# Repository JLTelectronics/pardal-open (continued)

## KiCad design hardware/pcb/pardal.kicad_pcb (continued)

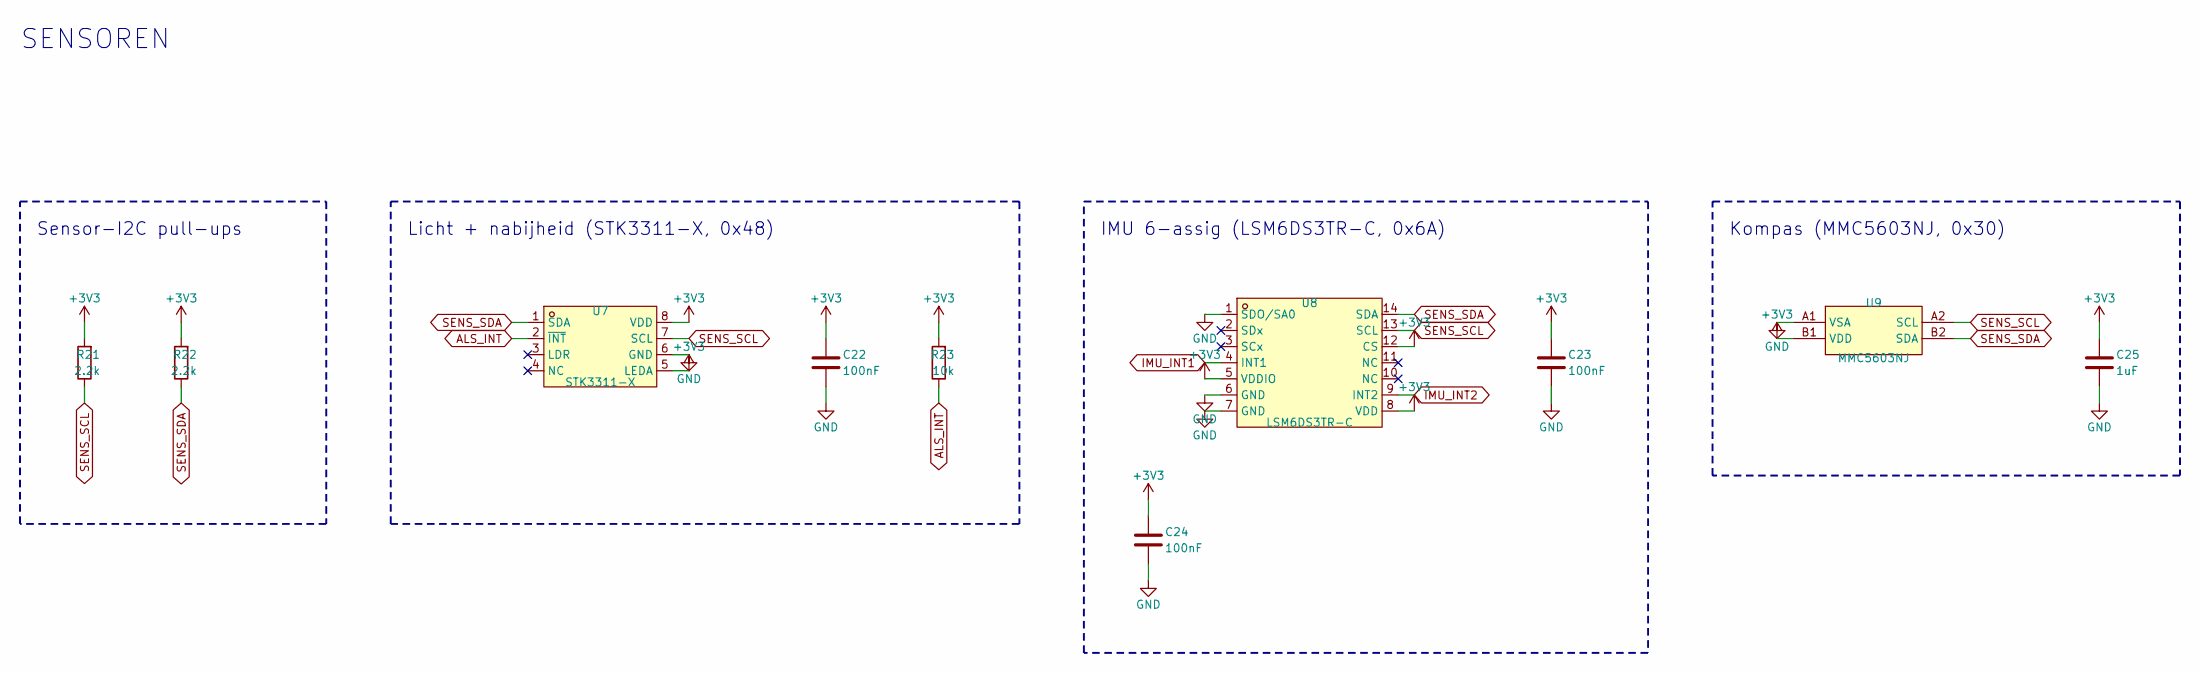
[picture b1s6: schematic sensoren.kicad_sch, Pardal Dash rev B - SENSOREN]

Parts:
C22, C23, C24: 100nF; C_0402_1005Metric; LCSC C1525
C25: 1uF; C_0402_1005Metric; LCSC C52923
R21, R22: 2.2k; R_0402_1005Metric; LCSC C25879
R23: 10k; R_0402_1005Metric; LCSC C25744
U7: STK3311-X; LGA-8_L4.0-W2.4-P0.97-BR; LCSC C966926
U8: LSM6DS3TR-C; LGA-14_L3.0-W2.5-P0.50-TL; LCSC C967633
U9: MMC5603NJ; FLIPCHIP-4_L0.8-W0.8-R2-C2-P0.40-TL; LCSC C404328

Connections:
+3V3: C22.1, C23.1, C24.1, C25.1, R21.2, R22.2, R23.2, U7.5 (LEDA), U7.8 (VDD), U8.5 (VDDIO), U8.8 (VDD), U8.12 (CS), U9.B1 (VDD); also elsewhere on the board
ALS_INT: R23.1, U7.2 (~INT); also elsewhere on the board
GND: C22.2, C23.2, C24.2, C25.2, U7.6 (GND), U8.1 (SDO/SA0), U8.6 (GND), U8.7 (GND), U9.A1 (VSA); also elsewhere on the board
IMU_INT1: U8.4 (INT1); also elsewhere on the board
IMU_INT2: U8.9 (INT2); also elsewhere on the board
SENS_SCL: R21.1, U7.7 (SCL), U8.13 (SCL), U9.A2 (SCL); also elsewhere on the board
SENS_SDA: R22.1, U7.1 (SDA), U8.14 (SDA), U9.B2 (SDA); also elsewhere on the board

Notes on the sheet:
SENSOREN
Sensor-I2C pull-ups
Licht + nabijheid (STK3311-X, 0x48)
IMU 6-assig (LSM6DS3TR-C, 0x6A)
Kompas (MMC5603NJ, 0x30)

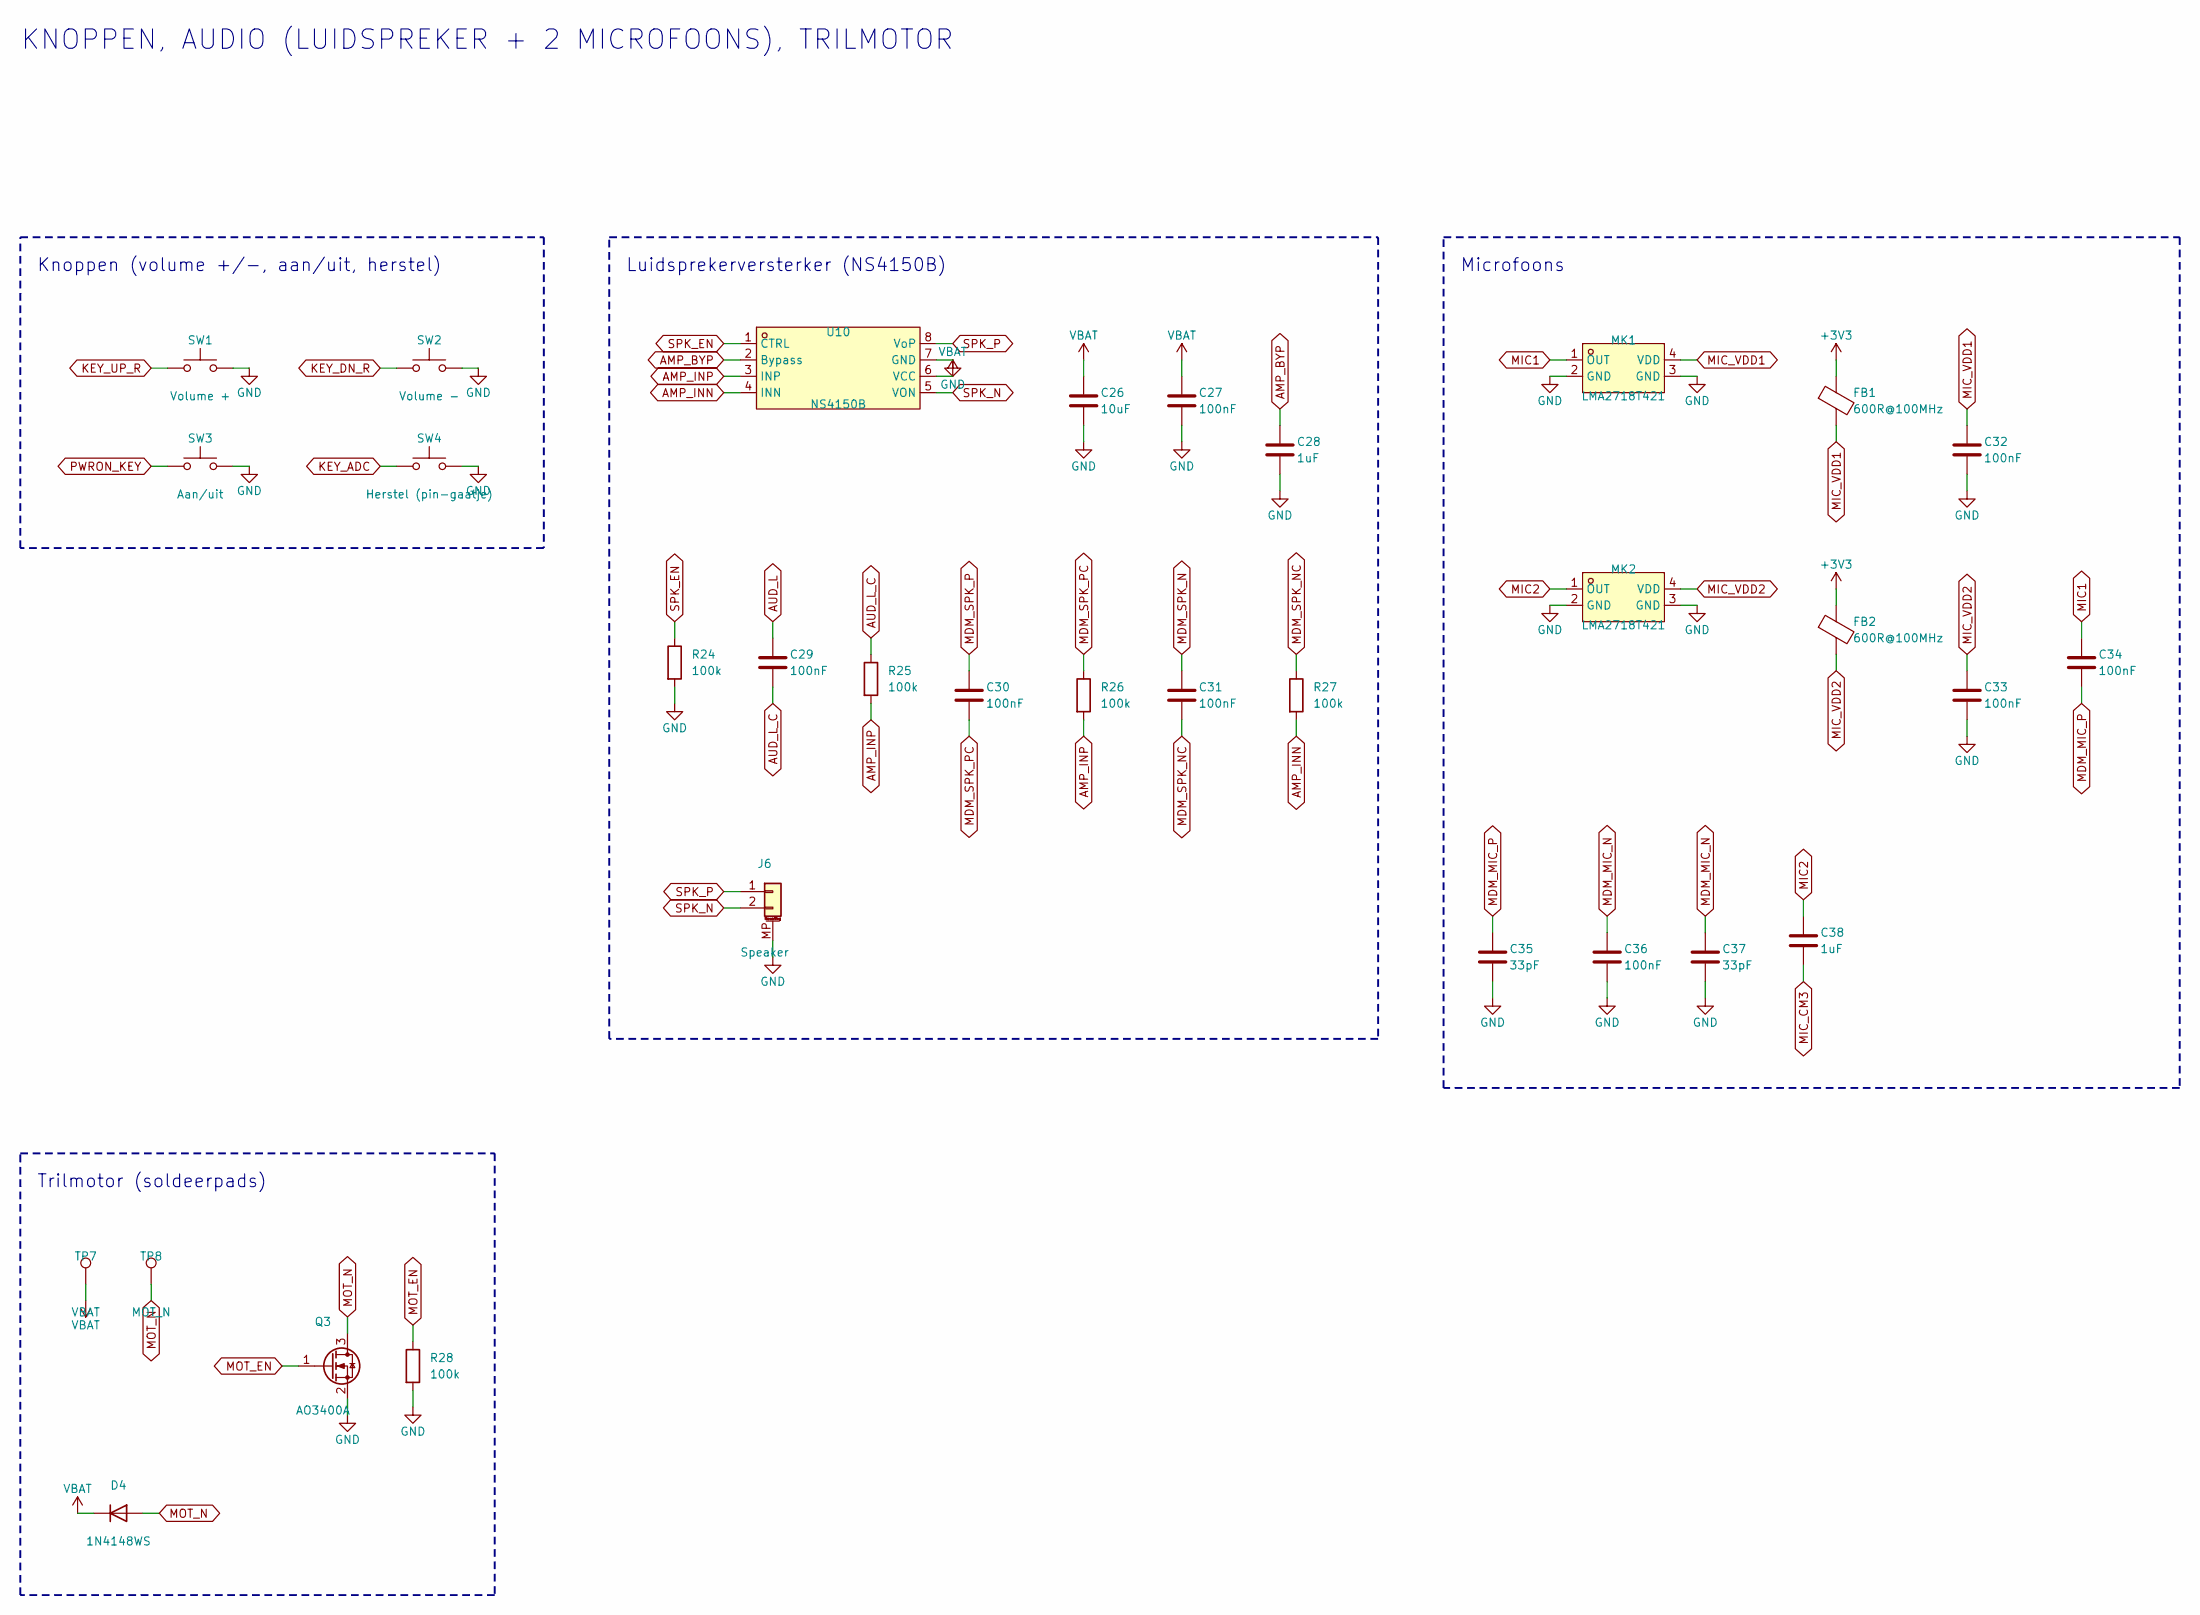
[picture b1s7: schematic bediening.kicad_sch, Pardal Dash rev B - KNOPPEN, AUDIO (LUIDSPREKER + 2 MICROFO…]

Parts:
C26: 10uF; C_0603_1608Metric; LCSC C19702
C27, C29, C30, C31, C32, C33, C34, C36: 100nF; C_0402_1005Metric; LCSC C1525
C28, C38: 1uF; C_0402_1005Metric; LCSC C52923
C35, C37: 33pF; C_0402_1005Metric; LCSC C1562
D4: 1N4148WS; D_SOD-323; LCSC C2128
FB1, FB2: 600R@100MHz; L_0402_1005Metric; LCSC C181004
J6: Speaker; JST_SH_SM02B-SRSS-TB_1x02-1MP_P1.00mm_Horizontal; LCSC C19271996
MK1, MK2: LMA2718T421; MIC-SMD_4P-L2.8-W1.9-P1.84-TL; LCSC C7587901
Q3: AO3400A; SOT-23; LCSC C20917
R24, R25, R26, R27, R28: 100k; R_0402_1005Metric; LCSC C25741
SW1: Volume +; SW_Push_1P1T-MP_NO_Horizontal_Alps_SKRTLAE010; LCSC C110293
SW2: Volume -; SW_Push_1P1T-MP_NO_Horizontal_Alps_SKRTLAE010; LCSC C110293
SW3: Aan/uit; SW_Push_1P1T_XKB_TS-1187A; LCSC C318884
SW4: Herstel (pin-gaatje); SW_SPST_TS-1088-xR020; LCSC C720477
TP7: VBAT; TestPoint_Pad_2.0x2.0mm
TP8: MOT_N; TestPoint_Pad_2.0x2.0mm
U10: NS4150B; MSOP-8_L3.0-W3.0-P0.65-LS5.0-BL; LCSC C189961

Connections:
+3V3: FB1.1, FB2.1; also elsewhere on the board
AMP_BYP: C28.1, U10.2 (Bypass)
AMP_INN: R27.2, U10.4 (INN)
AMP_INP: R25.2, R26.2, U10.3 (INP)
AUD_L: C29.1; also elsewhere on the board
AUD_L_C: C29.2, R25.1
GND: C26.2, C27.2, C28.2, C32.2, C33.2, C35.2, C36.2, C37.2, J6.MP (MountPin), MK1.2 (GND), MK1.3 (GND), MK2.2 (GND), MK2.3 (GND), Q3.2 (S), R24.2, R28.2, SW1.2, SW2.2, SW3.2, SW4.2, U10.7 (GND); also elsewhere on the board
KEY_ADC: SW4.1; also elsewhere on the board
KEY_DN_R: SW2.1; also elsewhere on the board
KEY_UP_R: SW1.1; also elsewhere on the board
MDM_MIC_N: C36.1, C37.1; also elsewhere on the board
MDM_MIC_P: C34.2, C35.1; also elsewhere on the board
MDM_SPK_N: C31.1; also elsewhere on the board
MDM_SPK_NC: C31.2, R27.1
MDM_SPK_P: C30.1; also elsewhere on the board
MDM_SPK_PC: C30.2, R26.1
MIC1: C34.1, MK1.1 (OUT)
MIC2: C38.1, MK2.1 (OUT)
MIC_CM3: C38.2; also elsewhere on the board
MIC_VDD1: C32.1, FB1.2, MK1.4 (VDD)
MIC_VDD2: C33.1, FB2.2, MK2.4 (VDD)
MOT_EN: Q3.1 (G), R28.1; also elsewhere on the board
MOT_N: D4.2 (A), Q3.3 (D), TP8.1
PWRON_KEY: SW3.1; also elsewhere on the board
SPK_EN: R24.1, U10.1 (CTRL); also elsewhere on the board
SPK_N: J6.2, U10.5 (VON)
SPK_P: J6.1, U10.8 (VoP)
VBAT: C26.1, C27.1, D4.1 (K), TP7.1, U10.6 (VCC); also elsewhere on the board

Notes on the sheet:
KNOPPEN, AUDIO (LUIDSPREKER + 2 MICROFOONS), TRILMOTOR
Knoppen (volume +/-, aan/uit, herstel)
Luidsprekerversterker (NS4150B)
Microfoons
Trilmotor (soldeerpads)

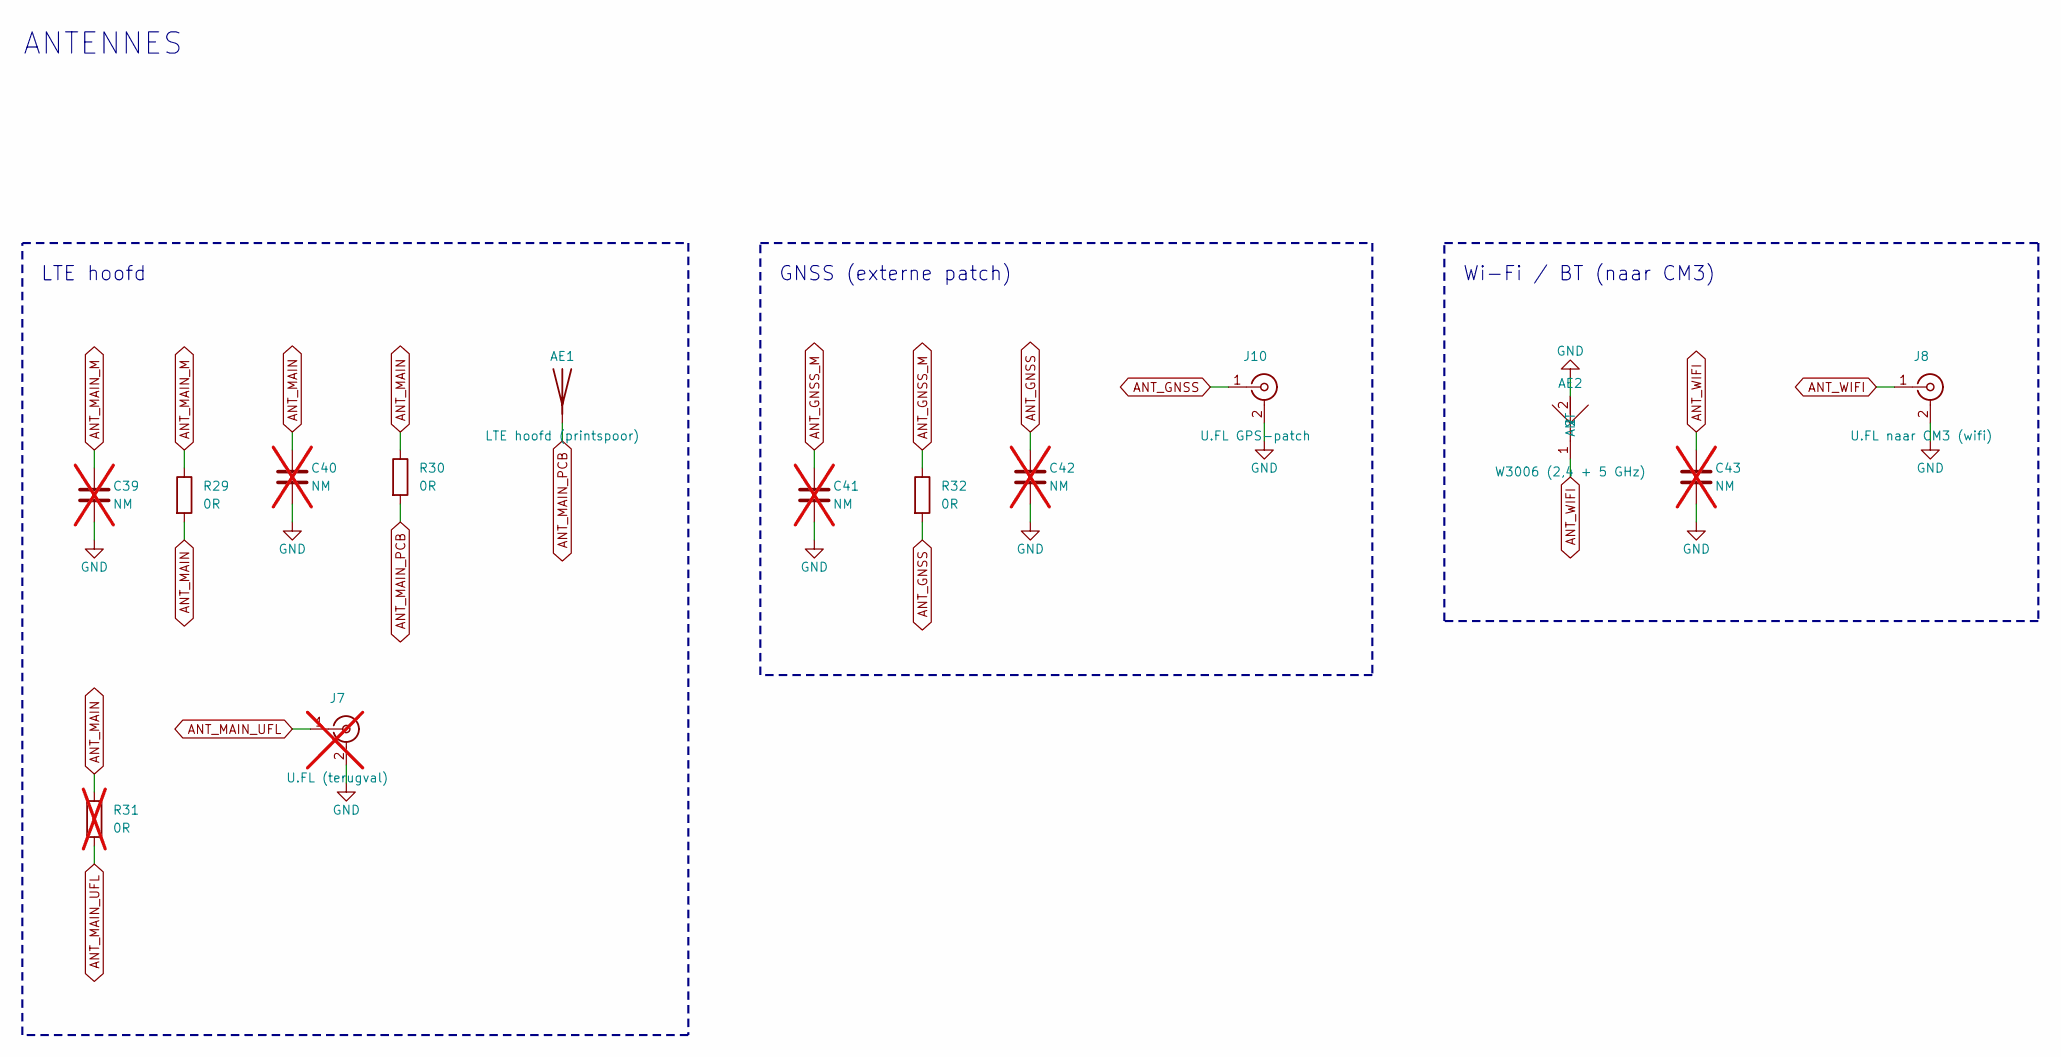
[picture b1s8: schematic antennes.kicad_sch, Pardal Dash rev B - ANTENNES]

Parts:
AE1: LTE hoofd (printspoor); LTE_meander_hoofd
AE2: W3006 (2,4 + 5 GHz); ANT-SMD_L10.0-W3.2; LCSC C5123155
C39, C40, C41, C42, C43: NM; C_0402_1005Metric; not fitted
J7: U.FL (terugval); U.FL_Hirose_U.FL-R-SMT-1_Vertical; LCSC C5299419; not fitted
J8: U.FL naar CM3 (wifi); U.FL_Hirose_U.FL-R-SMT-1_Vertical; LCSC C5299419
J10: U.FL GPS-patch; U.FL_Hirose_U.FL-R-SMT-1_Vertical; LCSC C5299419
R29, R30, R32: 0R; R_0402_1005Metric; LCSC C17168
R31: 0R; R_0402_1005Metric; LCSC C17168; not fitted

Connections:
ANT_GNSS: C42.1, J10.1 (In), R32.2
ANT_GNSS_M: C41.1, R32.1; also elsewhere on the board
ANT_MAIN: C40.1, R29.2, R30.1, R31.1
ANT_MAIN_M: C39.1, R29.1; also elsewhere on the board
ANT_MAIN_PCB: AE1.1, R30.2
ANT_MAIN_UFL: J7.1 (In), R31.2
ANT_WIFI: AE2.1 (ANT), C43.1, J8.1 (In)
GND: AE2.2, C39.2, C40.2, C41.2, C42.2, C43.2, J7.2 (Ext), J8.2 (Ext), J10.2 (Ext); also elsewhere on the board

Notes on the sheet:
ANTENNES
LTE hoofd
GNSS (externe patch)
Wi-Fi / BT (naar CM3)

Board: 6 copper layers, 130 parts (40 on the bottom side), 86 nets, no tracks yet.

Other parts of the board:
H1, H2, H3: MountingHole_2.2mm_M2_Pad_Via
H4, H5, H6, H7: MountingHole_2.7mm_M2.5_Pad_Via
